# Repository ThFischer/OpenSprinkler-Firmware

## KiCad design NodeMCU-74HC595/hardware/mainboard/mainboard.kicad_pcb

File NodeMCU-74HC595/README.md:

# OpenSprinkler-Firmware for NodeMCU Lua Lolin V3 with 74HC595 and 8 channel Relay Board
> This Firmware is a slightly modified variant of the original OpenSprinkler firmware
> to run with an inexpensive NodeMCU and a 8 Channels Relay Module

## Supported Features:
* 8 OpenSprinkler station, controlled by the board relays
* 3 Buttons
* OLED Display (SSD1306, 128x64)
* Real Time Clock DS1307
* 2 Sensor connectors 

## Known Restrictions
* Only 8 sprinkler stations are supported (but easy to modify to support daisy-chained shift registers)
  For more details [see here](https://weworkweplay.com/play/practical-guide-to-shift-registers/)  
* RF Transmitter not supported yet
* Current sensing is not supported (disabled on the OLED display)

## Used Hardware
* [NodeMCU Lua Lolin V3](https://www.ebay.com/sch/i.html?_from=R40&_nkw=nodemcu+lua+lolin+v3+CH340&_sacat=0&LH_TitleDesc=0&_sop=12)
* [8CH Channel 5V Relay Module](https://www.ebay.com/sch/i.html?_from=R40&_nkw=8ch+relay+board+5v+blue&_sacat=0&LH_TitleDesc=0&_sop=12)
* [128x64 OLED Display (SSD1306)](https://www.ebay.com/sch/i.html?&_nkw=128x64+OLED+Display+SSD1306&_sop=15)
* [Real Time Clock (DS1307)](https://www.ebay.com/sch/i.html?_from=R40&_nkw=DS1307+I2C+RTC+Module&_sacat=0&_sop=15)  
  Since this is a 5V module it's important to remove the pull up resistors (5V!) on SDA and SCL.  
    
  It's also important to use a rechargeable battery LIR2332!
* [Push Buttons](https://www.conrad.com/p/diptronics-dtsm-66n-v-b-pushbutton-12-v-dc-005-a-1-x-offon-momentary-1-pcs-707570)
* 5V DC Power Supply (e.g. Common USB Charger)  
  Since the NodeMCU has no 5V output pin you can't use the USB-Port of the NodeMCU.
  Just connect the USB cable directly (`GND` and `VIN`)
* Valve Power Supply (e.g. [24V~Bell-Transformer](https://www.amazon.de/-/en/JCL-BT8-8-Brand-Bell-Transformer/dp/B00K1CWEUG), in case you use 24V AC valves.)  
  **Important:** If you want to turn on the transformer via a relay (as OpenSprinkler  Master Zone) you should consider to use a ["RC Circuit" aka "Snubber"](https://www.ebay.com/sch/i.html?_from=R40&_trksid=p2047675.m570.l1313&_nkw=Absorption+Snubber+Circuit&_sacat=0) to protect the relay contacts.  
  
## Wiring
```
                                                                                         ┌────────────────┐  
                    ┌─────────────────┐                   ┌───────────────────┐         ─┤GND             │  
           SCL   ◄──┤D1             D6├───────────────────┤CLOCK            Q0├──────────┤IN1   8 ch.     │  
           SDA   ◄──┤D2   NodeMCU   D5├───────────────────┤LATCH  74HC595   Q1├──────────┤IN2   Relay     │  
                    │    Lua Lolin  D0├───────────────────┤DATA    Shift    Q2├──────────┤IN3   Board     │  
 GND ◄── Button1 ◄──┤D4     v3        │                   │       Register  Q3├──────────┤IN4             │  
 GND ◄── Button2 ◄──┤D3               │            GND ◄──┤/OE              Q4├──────────┤IN5             │  
3.3V ◄── Button3 ◄──┤D8               │           3.3V ◄──┤RESET            Q5├──────────┤IN6             │  
                    │               3V├──► 3.3V    GND ◄──┤GND              Q3├──────────┤IN4             │  
 GND ◄── Sensor1 ◄──┤D7            GND├──► GND    3.3V ◄──┤VCC              Q6├──────────┤IN7             │  
 GND ◄── Sensor2 ◄──┤RX            VIN├──► 5V             │                 Q4├──────────┤IN5             │  
                    └─────────────────┘                   │                 Q7├──────────┤IN8             │  
                                                          └───────────────────┘  3.3V ◄──┤VCC             │  
                                                                                         │                │  
                    ┌─────────────────┐              ┌─────────────────┐          GND ◄──┤GND             │  
             SCL ◄──┤SCL              │       SCL ◄──┤SCL              │                ─┤VCC             │  
             SDA ◄──┤SDA  I2C Display │       SDA ◄──┤SDA    I2C RTC   │           5V ◄──┤JD-VCC          │  
            3.3V ◄──┤VCC   128x64 px  │      3.3V ◄──┤VCC    DS1307    │                 └────────────────┘  
             GND ◄──┤GND              │       GND ◄──┤GND              │  
                    └─────────────────┘              └─────────────────┘   
```

## Used Software
  * [Visual Studio Code](https://code.visualstudio.com/download)
  * [PlatformIO IDE Extension](https://platformio.org/install/ide?install=vscode)

## Building and flashing the firmware
* In PlatformIO select the "nodemcu_74HC595" task of the Project
* Unplug the external 5V power supply and the sensors
* Connect the NodeMCU via USB cable to you computer
* Build and upload the Firmware
* Press the RST button of the NodeMCU
* Follow the instructions of the [OpenSprinkler User Manual](https://opensprinklershop.de/wp-content/uploads/2020/05/os-manual_2.1.9.pdf)

## PCBs
I used two PCBs (see [hardware](./hardware) folder for KiCad and PDF files):

* A "mainboard" to wire the the NodeMCU with connectors for all other modules  

* The "74HC595-adapter" to wire up a [SparkFun Shift Register Breakout - 74HC595](https://www.sparkfun.com/products/10680) with the mainboard and the [8CH Channel 5V Relay Module](https://www.ebay.com/sch/i.html?_from=R40&_nkw=8ch+relay+board+5v+blue&_sacat=0&LH_TitleDesc=0&_sop=12) (and optionally other daisy-chained relay boards).  

## Wi-Fi improvements:
If the Wi-Fi connectivity is poor you can add an [external antenna](https://www.amazon.de/gp/product/B07SSYSZM9) like I did in [another project](../README.md).  
See also [External Antenna for ESP8266](https://www.instructables.com/External-Antenna-for-ESP8266/) for more details.

## Meta

Distributed under the GNU General Public License license. See [LICENSE.txt](LICENSE.txt) for more information.

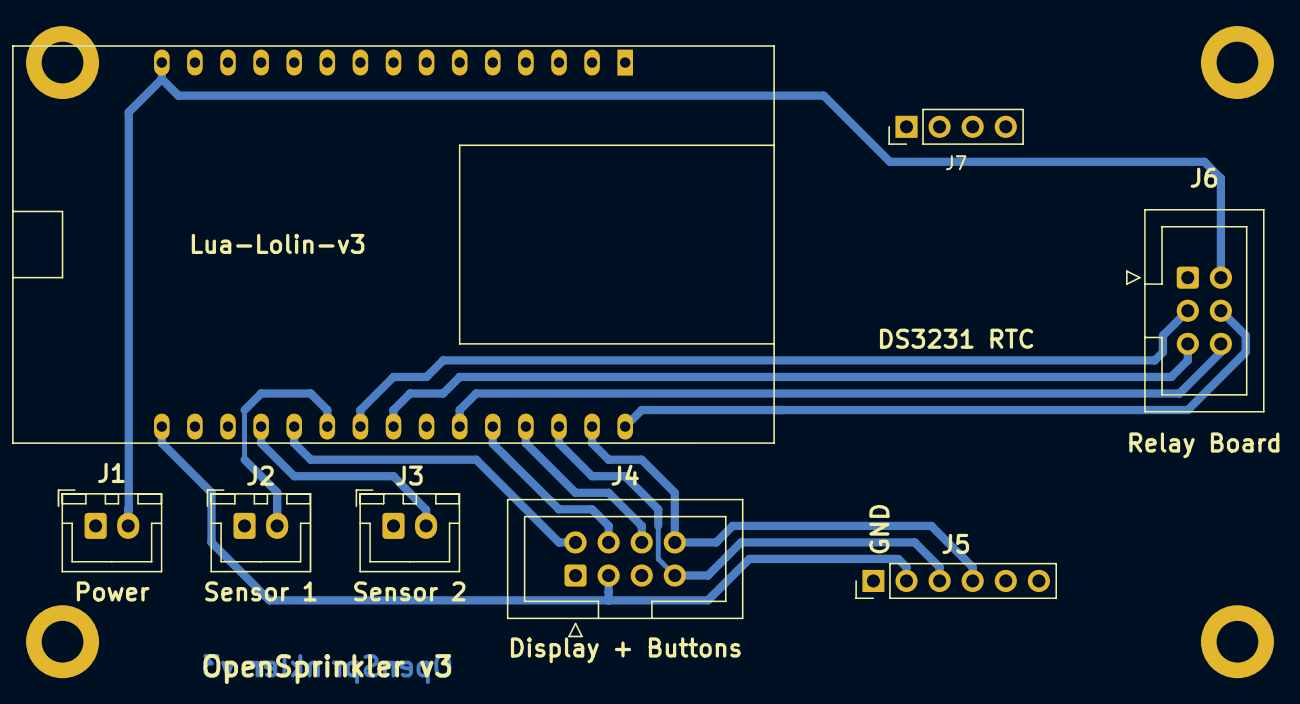
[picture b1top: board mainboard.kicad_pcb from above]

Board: 2 copper layers, 12 parts (0 on the bottom side), 14 nets.

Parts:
H1, H2, H3, H4: MountingHole; MountingHole_3.2mm_M3_DIN965_Pad
J1: Power; JST_XH_B2B-XH-A_1x02_P2.50mm_Vertical
J2: Sensor 1; JST_XH_B2B-XH-A_1x02_P2.50mm_Vertical
J3: Sensor 2; JST_XH_B2B-XH-A_1x02_P2.50mm_Vertical
J4: Display + Buttons; IDC-Header_2x04_P2.54mm_Vertical
J5: DS3231 RTC; PinHeader_1x06_P2.54mm_Vertical
J6: Relay Board; IDC-Header_2x03_P2.54mm_Vertical
J7: Conn_01x04_Female; PinHeader_1x04_P2.54mm_Vertical
U1: Lua-Lolin-v3; lua-lolin-v3

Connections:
/3V_2: J4.3, J5.2, U1.16
/3V_3: J6.6, U1.25
/5V: J1.2, J6.2, U1.15
/B1: J4.4, U1.26
/B2: J4.6, U1.27
/B3: J4.2, U1.20
/Clock: J6.3, U1.22
/Data: J6.4, U1.30
/GND: J1.1, J2.1, J3.1, J4.1, J5.1, J6.1, U1.2, U1.10, U1.14, U1.17
/Latch: J6.5, U1.23
/SCL: J4.8, J5.4, U1.29
/SDA: J4.7, J5.3, U1.28
/Sens1: J2.2, U1.21
/Sens2: J3.2, U1.19

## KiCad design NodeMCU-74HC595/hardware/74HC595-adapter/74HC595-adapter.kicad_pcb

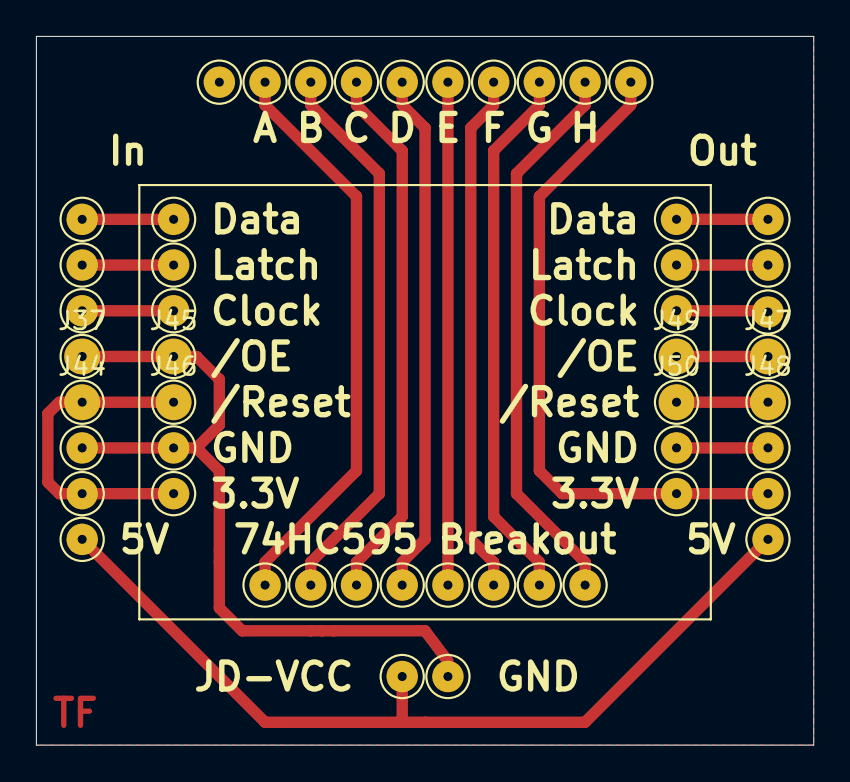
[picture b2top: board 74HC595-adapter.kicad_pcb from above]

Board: 2 copper layers, 43.2 x 39.4 mm, 50 parts (0 on the bottom side), 21 nets.

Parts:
J1, J2, J3, J4, J5, J6, J7, J8, J9, J10, J11, J12, J13, J14, J15, J16, J17, J18, J19, J20, J21, J22, J23, J24, J25, J26, J27, J28, J29, J30, J31, J32, J33, J34, J35, J36, J37, J38, J39, J40, J41, J42, J43, J44, J45, J46, J47, J48, J49, J50: Conn_01x01_Male; TestPoint_Pad_D2.0mm

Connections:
/3.3V1: J6.1, J13.1, J44.1, J46.1
/3.3V2: J31.1, J36.1, J42.1
/5V: J5.1, J8.1, J43.1
/A: J15.1, J16.1
/B: J17.1, J18.1
/C: J19.1, J20.1
/Clock1: J3.1, J11.1
/Clock2: J34.1, J40.1
/D: J21.1, J22.1
/Data1: J1.1, J9.1
/Data2: J32.1, J38.1
/E: J23.1, J24.1
/F: J25.1, J26.1
/G: J27.1, J28.1
/GND1: J4.1, J7.1, J12.1, J37.1, J45.1
/GND2: J35.1, J41.1
/H: J29.1, J30.1
/Latch1: J2.1, J10.1
/Latch2: J33.1, J39.1
/OE2: J47.1, J49.1
/Reset2: J48.1, J50.1

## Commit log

2021-10-27 Initial commit for NodeMCU-74HC595 branch
2021-10-27 Add readme.md
2021-10-27 Fix README.md
2022-01-09 * Add KiCad Schematic & PCB * Change Sensor GPIOs
2022-09-18 add KiCd files, improve ReadMe
2022-09-18 Improve ReadMe
2022-09-18 fix kicad
2022-09-18 clean hardware folders
2022-09-18 Update to KiCad 6, improve ReadMe
